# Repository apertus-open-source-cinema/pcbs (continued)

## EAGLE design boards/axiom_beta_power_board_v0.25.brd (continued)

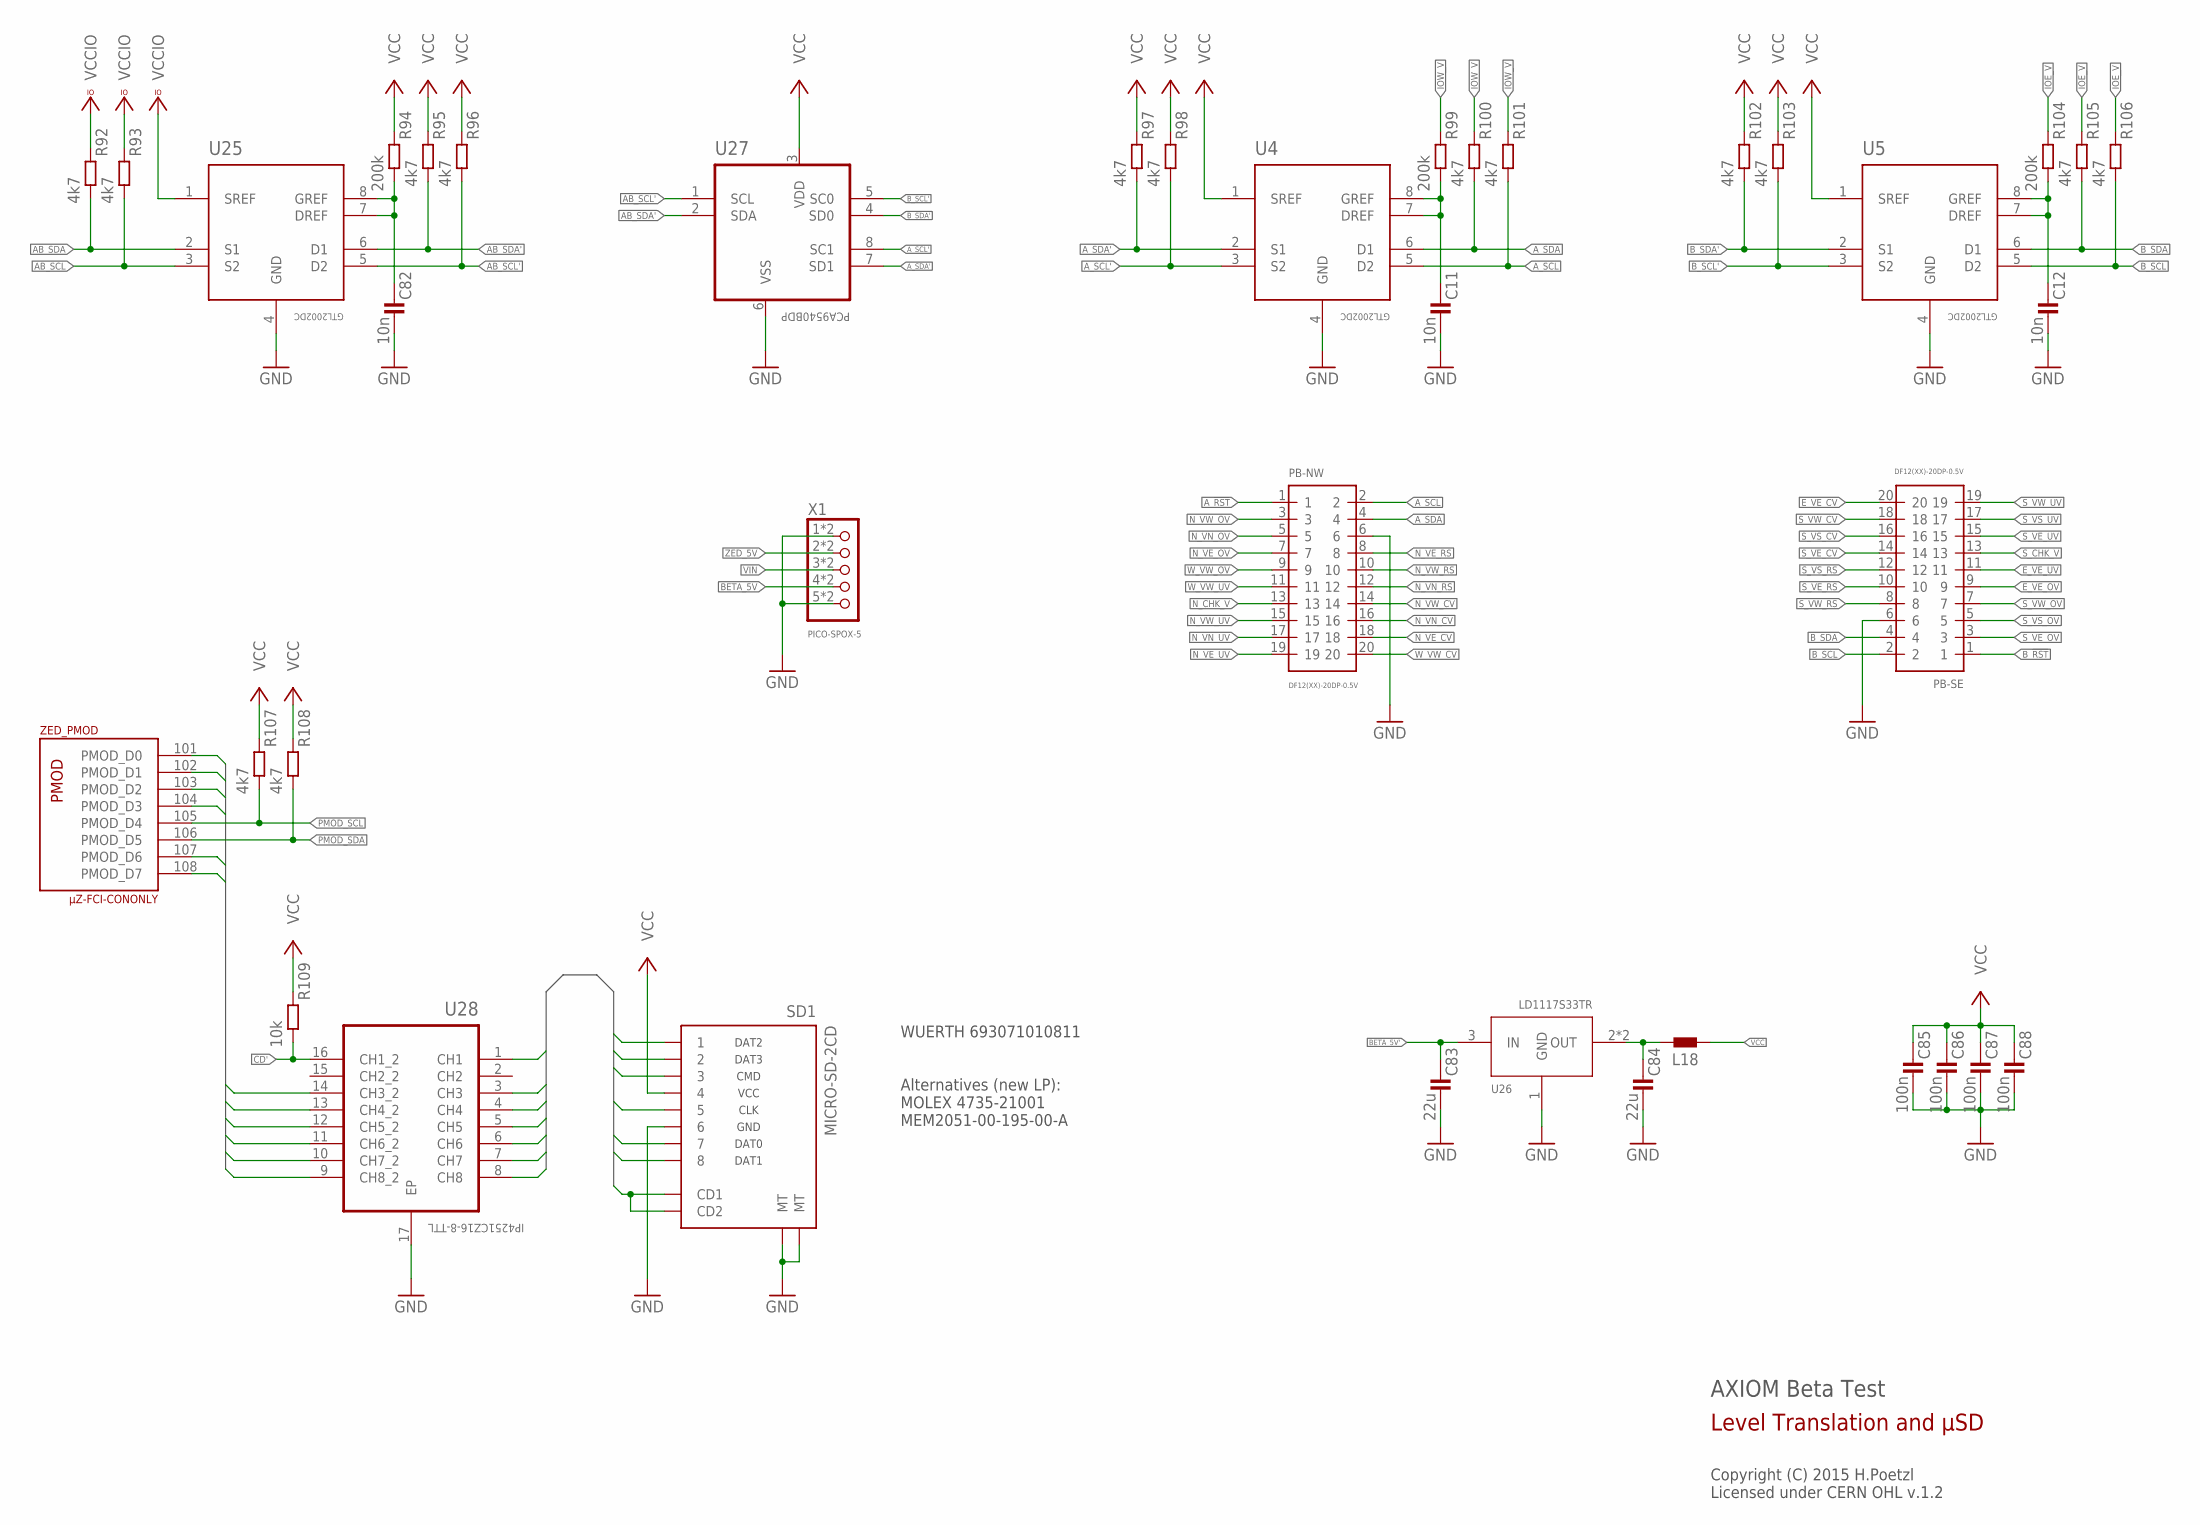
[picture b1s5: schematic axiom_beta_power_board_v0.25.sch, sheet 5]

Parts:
C11, C12, C82: 10n; 0402-B
C83, C84: 22u; 0805-B
C85, C86, C87, C88: 100n; 0402-B
L18: L0805-A; 0805-A
PB-NW: DF12(XX)-20DP-0.5V
PB-SE: DF12(XX)-20DP-0.5V
R92, R93, R95, R96, R97, R98, R100, R101, R102, R103, R105, R106, R107, R108: 4k7; 0402-B
R94, R99, R104: 200k; 0402-B
R109: 10k; 0402-B
SD1: MICRO-SD-2CD; TF-MICRO-SD_PP2
U4, U5, U25: GTL2002DC; VSSOP-8
U26: LD1117S33TR; SOT-223
U27: PCA9540BDP; SOP65P490X300-8N
U28: IP4251CZ16-8-TTL; SON40P135X330X55-17N
X1: PICO-SPOX-5
ZED: µZ-FCI-CONONLY; µZ-CONONLY

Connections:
AB_SCL: R93.2, U25.3 (S2); also elsewhere on the board
AB_SCL': R96.2, U25.5 (D2), U27.1 (SCL)
AB_SDA: R92.2, U25.2 (S1); also elsewhere on the board
AB_SDA': R95.2, U25.6 (D1), U27.2 (SDA)
A_!RST: PB-NW.1; also elsewhere on the board
A_SCL: PB-NW.2, R101.2, U4.5 (D2)
A_SCL': R98.2, U4.3 (S2), U27.8 (SC1)
A_SDA: PB-NW.4, R100.2, U4.6 (D1)
A_SDA': R97.2, U4.2 (S1), U27.7 (SD1)
BETA_5V: X1.4, X1.4A (4); also elsewhere on the board
BETA_5V': C83.1, U26.3 (IN); also elsewhere on the board
B_!RST: PB-SE.1; also elsewhere on the board
B_SCL: PB-SE.2, R106.2, U5.5 (D2)
B_SCL': R103.2, U5.3 (S2), U27.5 (SC0)
B_SDA: PB-SE.4, R105.2, U5.6 (D1)
B_SDA': R102.2, U5.2 (S1), U27.4 (SD0)
CD: SD1.CD1, SD1.CD2, U28.1 (CH1)
CD': R109.2, U28.16 (CH1_2); also elsewhere on the board
CLK: SD1.5, U28.6 (CH6)
CMD: SD1.3, U28.5 (CH5)
DAT0: SD1.7, U28.7 (CH7)
DAT1: SD1.8, U28.8 (CH8)
DAT2: SD1.1, U28.3 (CH3)
DAT3: SD1.2, U28.4 (CH4)
E_VE_CV: PB-SE.20
E_VE_OV: PB-SE.9
E_VE_UV: PB-SE.11
GND: C11.2, C12.2, C82.2, C83.2, C84.2, C85.2, C86.2, C87.2, C88.2, PB-NW.6, PB-SE.6, SD1.6, SD1.MT1 (MT), SD1.MT2 (MT), U4.4 (GND), U5.4 (GND), U25.4 (GND), U26.1 (GND), U27.6 (VSS), U28.17 (EP), X1.1, X1.1A (1), X1.5, X1.5A (5); also elsewhere on the board
IOE_V: R104.1, R105.1, R106.1; also elsewhere on the board
IOW_V: R99.1, R100.1, R101.1; also elsewhere on the board
unnamed: C11.1, R99.2, U4.7 (DREF), U4.8 (GREF)
unnamed: C12.1, R104.2, U5.7 (DREF), U5.8 (GREF)
unnamed: C82.1, R94.2, U25.7 (DREF), U25.8 (GREF)
N_CHK_V: PB-NW.13
N_VE_CV: PB-NW.18
N_VE_OV: PB-NW.7
N_VE_RS: PB-NW.8
N_VE_UV: PB-NW.19
N_VN_CV: PB-NW.16
N_VN_OV: PB-NW.5
N_VN_RS: PB-NW.12
N_VN_UV: PB-NW.17
N_VW_CV: PB-NW.14
N_VW_OV: PB-NW.3
N_VW_RS: PB-NW.10
N_VW_UV: PB-NW.15
PMOD_D0: U28.9 (CH8_2), ZED.101 (PMOD_D0)
PMOD_D1: U28.10 (CH7_2), ZED.102 (PMOD_D1)
PMOD_D2: U28.12 (CH5_2), ZED.103 (PMOD_D2)
PMOD_D3: U28.11 (CH6_2), ZED.104 (PMOD_D3)
PMOD_D6: U28.14 (CH3_2), ZED.107 (PMOD_D6)
PMOD_D7: U28.13 (CH4_2), ZED.108 (PMOD_D7)
PMOD_SCL: R107.2, ZED.105 (PMOD_D4); also elsewhere on the board
PMOD_SDA: R108.2, ZED.106 (PMOD_D5); also elsewhere on the board
REGOUT: C84.1, L18.1, U26.2 (OUT), U26.TER (OUT)
S_CHK_V: PB-SE.13
S_VE_CV: PB-SE.14
S_VE_OV: PB-SE.3
S_VE_RS: PB-SE.10
S_VE_UV: PB-SE.15
S_VS_CV: PB-SE.16
S_VS_OV: PB-SE.5
S_VS_RS: PB-SE.12
S_VS_UV: PB-SE.17
S_VW_CV: PB-SE.18
S_VW_OV: PB-SE.7
S_VW_RS: PB-SE.8
S_VW_UV: PB-SE.19
VCC: C85.1, C86.1, C87.1, C88.1, L18.2, R94.1, R95.1, R96.1, R97.1, R98.1, R102.1, R103.1, R107.1, R108.1, R109.1, SD1.4, U4.1 (SREF), U5.1 (SREF), U27.3 (VDD); also elsewhere on the board
VCCIO: R92.1, R93.1, U25.1 (SREF); also elsewhere on the board
VIN: X1.3, X1.3A (3)
W_VW_CV: PB-NW.20
W_VW_OV: PB-NW.9
W_VW_UV: PB-NW.11
ZED_5V: X1.2, X1.2A (2); also elsewhere on the board

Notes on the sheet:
AXIOM Beta Test
Copyright (C) 2015 H.Poetzl Licensed under CERN OHL v.1.2
Level Translation and µSD
WUERTH 693071010811 Alternatives (new LP): MOLEX 4735-21001 MEM2051-00-195-00-A

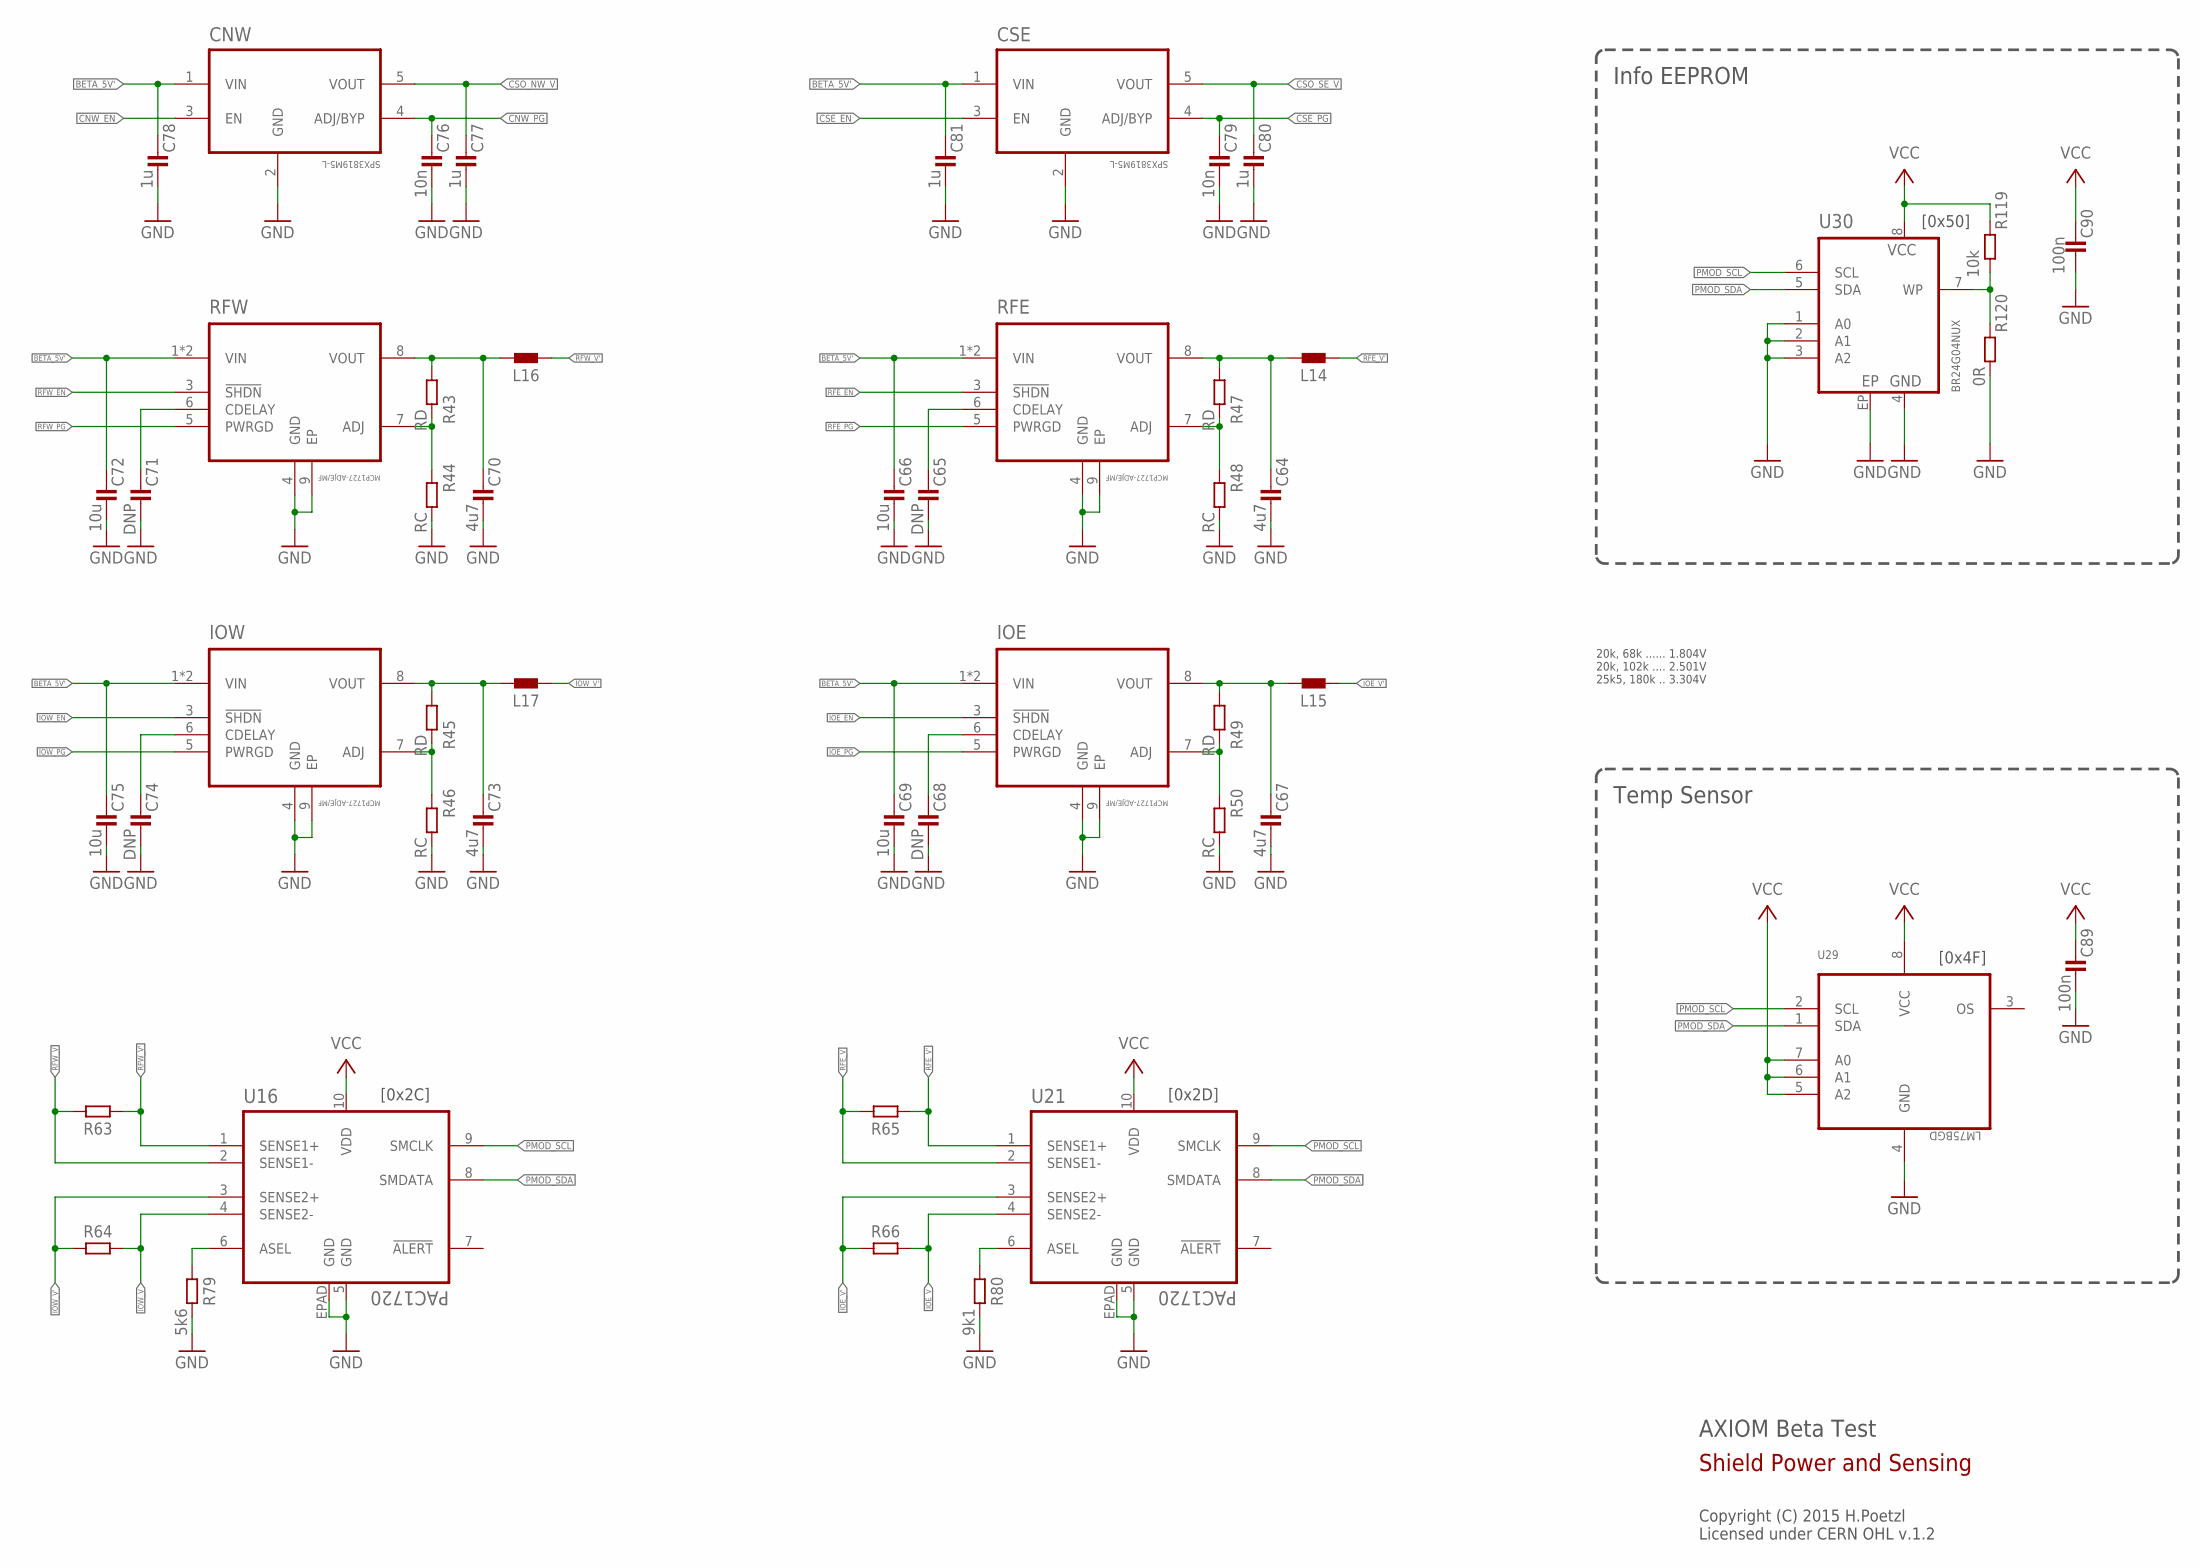
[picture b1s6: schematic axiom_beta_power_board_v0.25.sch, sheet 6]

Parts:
C64, C67, C70, C73: 4u7; 0603-B
C65, C68, C71, C74: DNP; 0402-B
C66, C69, C72, C75: 10u; 0603-B
C76, C79: 10n; 0402-B
C77, C78, C80, C81: 1u; 0402-B
C89, C90: 100n; 0402-B
CNW: SPX3819M5-L; SOT95P280X145-5N
CSE: SPX3819M5-L; SOT95P280X145-5N
IOE: MCP1727-ADJE/MF; DFN65P300X300X100-9N
IOW: MCP1727-ADJE/MF; DFN65P300X300X100-9N
L14, L15, L16, L17: L0805-B; 0805-B
R43, R45, R47, R49: RD; 0402-B
R44, R46, R48, R50: RC; 0402-B
R63, R64, R65, R66: R1206-B; 1206-B
R79: 5k6; 0402-B
R80: 9k1; 0402-B
R119: 10k; 0402-B
R120: 0R; 0402-B
RFE: MCP1727-ADJE/MF; DFN65P300X300X100-9N
RFW: MCP1727-ADJE/MF; DFN65P300X300X100-9N
U16, U21: PAC1720; DFN3X3_10LEAD
U29: LM75BGD; SOT996-2/3
U30: BR24G04NUX; DFN200X300X100-9N

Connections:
BETA_5V': C66.1, C69.1, C72.1, C75.1, C78.1, C81.1, CNW.1 (VIN), CSE.1 (VIN), IOE.1 (VIN), IOE.2 (VIN), IOW.1 (VIN), IOW.2 (VIN), RFE.1 (VIN), RFE.2 (VIN), RFW.1 (VIN), RFW.2 (VIN); also elsewhere on the board
CNW_EN: CNW.3 (EN); also elsewhere on the board
CNW_PG: C76.1, CNW.4 (ADJ/BYP); also elsewhere on the board
CSE_EN: CSE.3 (EN); also elsewhere on the board
CSE_PG: C79.1, CSE.4 (ADJ/BYP); also elsewhere on the board
CSO_NW_V: C77.1, CNW.5 (VOUT); also elsewhere on the board
CSO_SE_V: C80.1, CSE.5 (VOUT); also elsewhere on the board
GND: C64.2, C65.2, C66.2, C67.2, C68.2, C69.2, C70.2, C71.2, C72.2, C73.2, C74.2, C75.2, C76.2, C77.2, C78.2, C79.2, C80.2, C81.2, C89.2, C90.2, CNW.2 (GND), CSE.2 (GND), IOE.4 (GND), IOE.9 (EP), IOW.4 (GND), IOW.9 (EP), R44.2, R46.2, R48.2, R50.2, R79.2, R80.2, R120.2, RFE.4 (GND), RFE.9 (EP), RFW.4 (GND), RFW.9 (EP), U16.5 (GND), U16.EPAD (GND), U21.5 (GND), U21.EPAD (GND), U29.4 (GND), U30.1 (A0), U30.2 (A1), U30.3 (A2), U30.4 (GND), U30.EP; also elsewhere on the board
IOE_EN: IOE.3 (!SHDN); also elsewhere on the board
IOE_PG: IOE.5 (PWRGD); also elsewhere on the board
IOE_V: R66.2, U21.4 (SENSE2-); also elsewhere on the board
IOE_V': L15.2, R66.1, U21.3 (SENSE2+)
IOW_EN: IOW.3 (!SHDN); also elsewhere on the board
IOW_PG: IOW.5 (PWRGD); also elsewhere on the board
IOW_V: R64.2, U16.4 (SENSE2-); also elsewhere on the board
IOW_V': L17.2, R64.1, U16.3 (SENSE2+)
unnamed: R119.2, R120.1, U30.7 (WP)
unnamed: C64.1, L14.1, R47.1, RFE.8 (VOUT)
unnamed: R47.2, R48.1, RFE.7 (ADJ)
unnamed: C65.1, RFE.6 (CDELAY)
unnamed: C67.1, IOE.8 (VOUT), L15.1, R49.1
unnamed: IOE.7 (ADJ), R49.2, R50.1
unnamed: C68.1, IOE.6 (CDELAY)
unnamed: C70.1, L16.1, R43.1, RFW.8 (VOUT)
unnamed: R43.2, R44.1, RFW.7 (ADJ)
unnamed: C71.1, RFW.6 (CDELAY)
unnamed: C73.1, IOW.8 (VOUT), L17.1, R45.1
unnamed: IOW.7 (ADJ), R45.2, R46.1
unnamed: C74.1, IOW.6 (CDELAY)
unnamed: R79.1, U16.6 (ASEL)
unnamed: R80.1, U21.6 (ASEL)
PMOD_SCL: U16.9 (SMCLK), U21.9 (SMCLK), U29.2 (SCL), U30.6 (SCL); also elsewhere on the board
PMOD_SDA: U16.8 (SMDATA), U21.8 (SMDATA), U29.1 (SDA), U30.5 (SDA); also elsewhere on the board
RFE_EN: RFE.3 (!SHDN); also elsewhere on the board
RFE_PG: RFE.5 (PWRGD); also elsewhere on the board
RFE_V: R65.2, U21.2 (SENSE1-); also elsewhere on the board
RFE_V': L14.2, R65.1, U21.1 (SENSE1+)
RFW_EN: RFW.3 (!SHDN); also elsewhere on the board
RFW_PG: RFW.5 (PWRGD); also elsewhere on the board
RFW_V: R63.2, U16.2 (SENSE1-); also elsewhere on the board
RFW_V': L16.2, R63.1, U16.1 (SENSE1+)
VCC: C89.1, C90.1, R119.1, U16.10 (VDD), U21.10 (VDD), U29.5 (A2), U29.6 (A1), U29.7 (A0), U29.8 (VCC), U30.8 (VCC); also elsewhere on the board

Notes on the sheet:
AXIOM Beta Test
Copyright (C) 2015 H.Poetzl Licensed under CERN OHL v.1.2
Shield Power and Sensing
20k, 68k ...... 1.804V 20k, 102k .... 2.501V 25k5, 180k .. 3.304V
[0x2C]
[0x2D]
[0x4F]
Info EEPROM
[0x50]
Temp Sensor

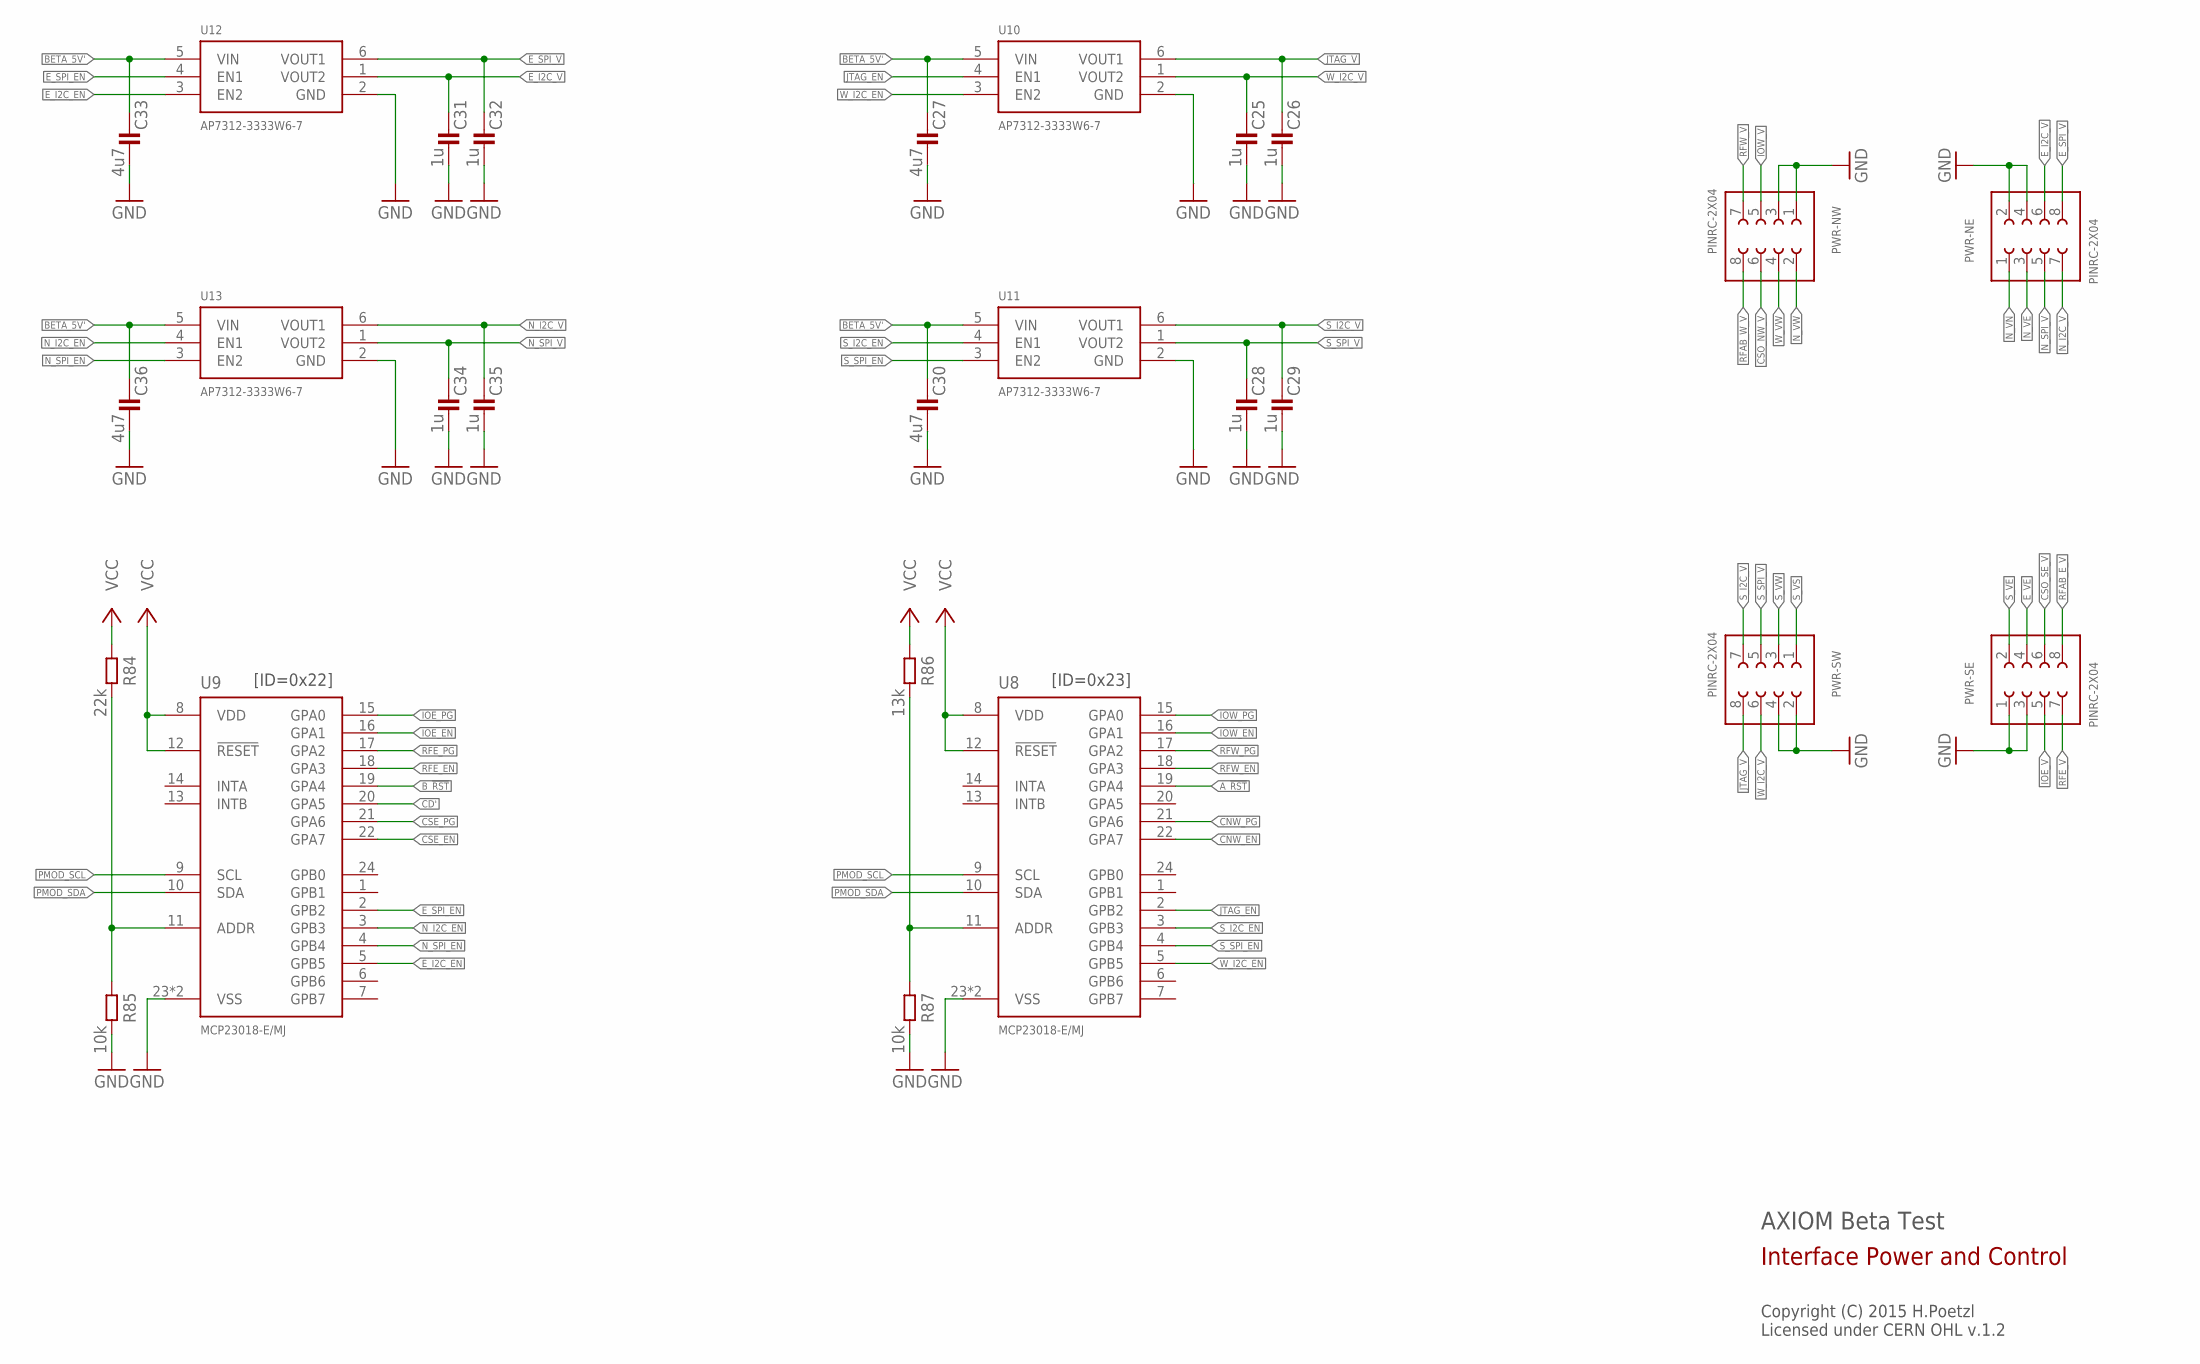
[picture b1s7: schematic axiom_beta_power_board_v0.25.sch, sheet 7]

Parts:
C25, C26, C28, C29, C31, C32, C34, C35: 1u; 0402-B
C27, C30, C33, C36: 4u7; 0603-B
PWR-NE: PINRC-2X04; R2X04
PWR-NW: PINRC-2X04; R2X04
PWR-SE: PINRC-2X04; R2X04
PWR-SW: PINRC-2X04; R2X04
R84: 22k; 0402-B
R85, R87: 10k; 0402-B
R86: 13k; 0402-B
U8, U9: MCP23018-E/MJ; QFN50P400X400X80-25N
U10, U11, U12, U13: AP7312-3333W6-7; SOT23-6

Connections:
A_!RST: U8.19 (GPA4); also elsewhere on the board
BETA_5V': C27.1, C30.1, C33.1, C36.1, U10.5 (VIN), U11.5 (VIN), U12.5 (VIN), U13.5 (VIN); also elsewhere on the board
B_!RST: U9.19 (GPA4); also elsewhere on the board
CD': U9.20 (GPA5); also elsewhere on the board
CNW_EN: U8.22 (GPA7); also elsewhere on the board
CNW_PG: U8.21 (GPA6); also elsewhere on the board
CSE_EN: U9.22 (GPA7); also elsewhere on the board
CSE_PG: U9.21 (GPA6); also elsewhere on the board
CSO_NW_V: PWR-NW.6; also elsewhere on the board
CSO_SE_V: PWR-SE.6; also elsewhere on the board
E_I2C_EN: U9.5 (GPB5), U12.3 (EN2)
E_I2C_V: C31.1, PWR-NE.6, U12.1 (VOUT2)
E_SPI_EN: U9.2 (GPB2), U12.4 (EN1)
E_SPI_V: C32.1, PWR-NE.8, U12.6 (VOUT1)
E_VE: PWR-SE.4; also elsewhere on the board
GND: C25.2, C26.2, C27.2, C28.2, C29.2, C30.2, C31.2, C32.2, C33.2, C34.2, C35.2, C36.2, PWR-NE.2, PWR-NE.4, PWR-NW.1, PWR-NW.3, PWR-SE.1, PWR-SE.3, PWR-SW.2, PWR-SW.4, R85.2, R87.2, U8.23 (VSS), U8.25 (VSS), U9.23 (VSS), U9.25 (VSS), U10.2 (GND), U11.2 (GND), U12.2 (GND), U13.2 (GND); also elsewhere on the board
IOE_EN: U9.16 (GPA1); also elsewhere on the board
IOE_PG: U9.15 (GPA0); also elsewhere on the board
IOE_V: PWR-SE.5; also elsewhere on the board
IOW_EN: U8.16 (GPA1); also elsewhere on the board
IOW_PG: U8.15 (GPA0); also elsewhere on the board
IOW_V: PWR-NW.5; also elsewhere on the board
JTAG_EN: U8.2 (GPB2), U10.4 (EN1)
JTAG_V: C26.1, PWR-SW.8, U10.6 (VOUT1)
unnamed: R84.2, R85.1, U9.11 (ADDR)
unnamed: R86.2, R87.1, U8.11 (ADDR)
N_I2C_EN: U9.3 (GPB3), U13.4 (EN1)
N_I2C_V: C35.1, PWR-NE.7, U13.6 (VOUT1)
N_SPI_EN: U9.4 (GPB4), U13.3 (EN2)
N_SPI_V: C34.1, PWR-NE.5, U13.1 (VOUT2)
N_VE: PWR-NE.3; also elsewhere on the board
N_VN: PWR-NE.1; also elsewhere on the board
N_VW: PWR-NW.2; also elsewhere on the board
PMOD_SCL: U8.9 (SCL), U9.9 (SCL); also elsewhere on the board
PMOD_SDA: U8.10 (SDA), U9.10 (SDA); also elsewhere on the board
RFAB_E_V: PWR-SE.8
RFAB_W_V: PWR-NW.8
RFE_EN: U9.18 (GPA3); also elsewhere on the board
RFE_PG: U9.17 (GPA2); also elsewhere on the board
RFE_V: PWR-SE.7; also elsewhere on the board
RFW_EN: U8.18 (GPA3); also elsewhere on the board
RFW_PG: U8.17 (GPA2); also elsewhere on the board
RFW_V: PWR-NW.7; also elsewhere on the board
S_I2C_EN: U8.3 (GPB3), U11.4 (EN1)
S_I2C_V: C29.1, PWR-SW.7, U11.6 (VOUT1)
S_SPI_EN: U8.4 (GPB4), U11.3 (EN2)
S_SPI_V: C28.1, PWR-SW.5, U11.1 (VOUT2)
S_VE: PWR-SE.2; also elsewhere on the board
S_VS: PWR-SW.1; also elsewhere on the board
S_VW: PWR-SW.3; also elsewhere on the board
VCC: R84.1, R86.1, U8.8 (VDD), U8.12 (!RESET), U9.8 (VDD), U9.12 (!RESET); also elsewhere on the board
W_I2C_EN: U8.5 (GPB5), U10.3 (EN2)
W_I2C_V: C25.1, PWR-SW.6, U10.1 (VOUT2)
W_VW: PWR-NW.4; also elsewhere on the board

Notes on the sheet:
AXIOM Beta Test
Copyright (C) 2015 H.Poetzl Licensed under CERN OHL v.1.2
Interface Power and Control
[ID=0x22]
[ID=0x23]

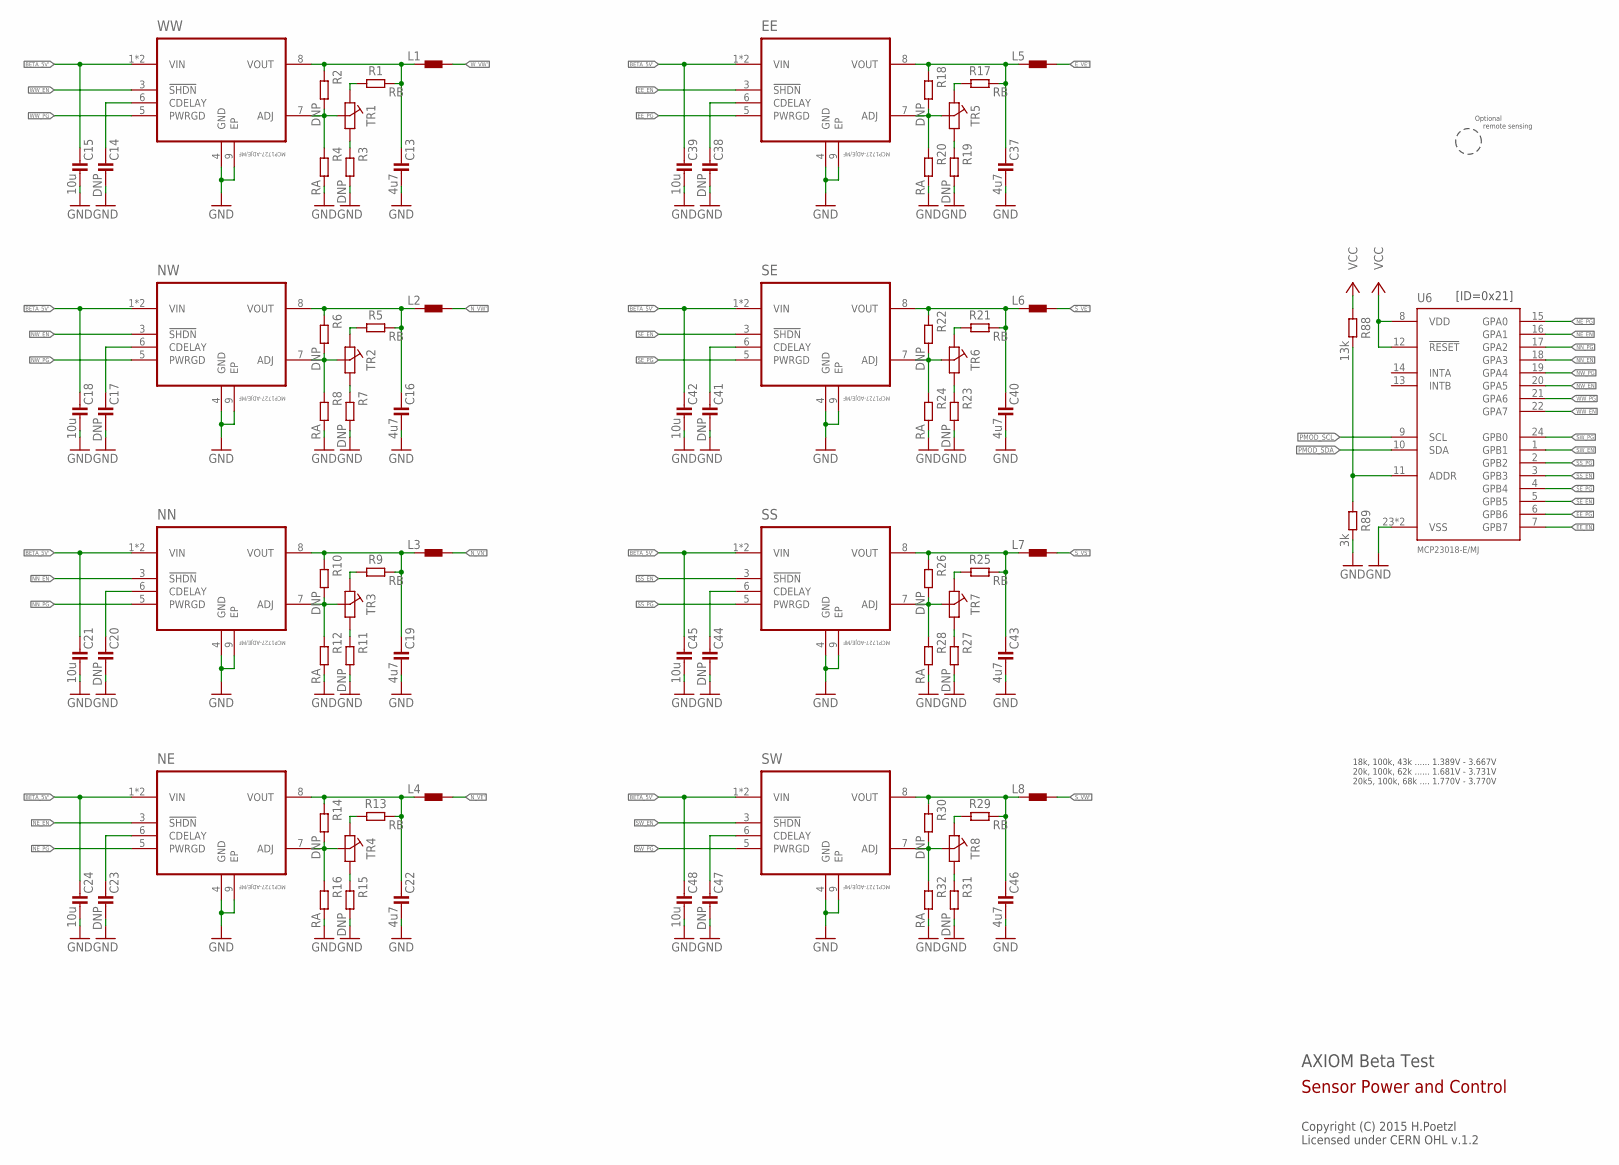
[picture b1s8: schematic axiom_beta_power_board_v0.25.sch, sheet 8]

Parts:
C13, C16, C19, C22, C37, C40, C43, C46: 4u7; 0603-B
C14, C17, C20, C23, C38, C41, C44, C47: DNP; 0402-B
C15, C18, C21, C24, C39, C42, C45, C48: 10u; 0603-B
EE: MCP1727-ADJE/MF; DFN65P300X300X100-9N
L1, L2, L3, L4, L5, L6, L7, L8: L0805-B; 0805-B
NE: MCP1727-ADJE/MF; DFN65P300X300X100-9N
NN: MCP1727-ADJE/MF; DFN65P300X300X100-9N
NW: MCP1727-ADJE/MF; DFN65P300X300X100-9N
R1, R5, R9, R13, R17, R21, R25, R29: RB; 0402-B
R2, R3, R6, R7, R10, R11, R14, R15, R18, R19, R22, R23, R26, R27, R30, R31: DNP; 0402-B
R4, R8, R12, R16, R20, R24, R28, R32: RA; 0402-B
R88: 13k; 0402-B
R89: 3k; 0402-B
SE: MCP1727-ADJE/MF; DFN65P300X300X100-9N
SS: MCP1727-ADJE/MF; DFN65P300X300X100-9N
SW: MCP1727-ADJE/MF; DFN65P300X300X100-9N
TR1, TR2, TR3, TR4, TR5, TR6, TR7, TR8: PVZ2A; TRIM-PVZ2A
U6: MCP23018-E/MJ; QFN50P400X400X80-25N
WW: MCP1727-ADJE/MF; DFN65P300X300X100-9N

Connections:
BETA_5V': C15.1, C18.1, C21.1, C24.1, C39.1, C42.1, C45.1, C48.1, EE.1 (VIN), EE.2 (VIN), NE.1 (VIN), NE.2 (VIN), NN.1 (VIN), NN.2 (VIN), NW.1 (VIN), NW.2 (VIN), SE.1 (VIN), SE.2 (VIN), SS.1 (VIN), SS.2 (VIN), SW.1 (VIN), SW.2 (VIN), WW.1 (VIN), WW.2 (VIN); also elsewhere on the board
EE_EN: EE.3 (!SHDN), U6.7 (GPB7)
EE_PG: EE.5 (PWRGD), U6.6 (GPB6)
E_VE': L5.2; also elsewhere on the board
GND: C13.2, C14.2, C15.2, C16.2, C17.2, C18.2, C19.2, C20.2, C21.2, C22.2, C23.2, C24.2, C37.2, C38.2, C39.2, C40.2, C41.2, C42.2, C43.2, C44.2, C45.2, C46.2, C47.2, C48.2, EE.4 (GND), EE.9 (EP), NE.4 (GND), NE.9 (EP), NN.4 (GND), NN.9 (EP), NW.4 (GND), NW.9 (EP), R3.2, R4.2, R7.2, R8.2, R11.2, R12.2, R15.2, R16.2, R19.2, R20.2, R23.2, R24.2, R27.2, R28.2, R31.2, R32.2, R89.2, SE.4 (GND), SE.9 (EP), SS.4 (GND), SS.9 (EP), SW.4 (GND), SW.9 (EP), U6.23 (VSS), U6.25 (VSS), WW.4 (GND), WW.9 (EP); also elsewhere on the board
unnamed: C13.1, L1.1, R1.2, R2.1, WW.8 (VOUT)
unnamed: R2.2, R4.1, TR1.2 (B), WW.7 (ADJ)
unnamed: R3.1, TR1.1 (A)
unnamed: C14.1, WW.6 (CDELAY)
unnamed: R1.1, TR1.3 (C)
unnamed: C16.1, L2.1, NW.8 (VOUT), R5.2, R6.1
unnamed: NW.7 (ADJ), R6.2, R8.1, TR2.2 (B)
unnamed: R7.1, TR2.1 (A)
unnamed: C17.1, NW.6 (CDELAY)
unnamed: C19.1, L3.1, NN.8 (VOUT), R9.2, R10.1
unnamed: NN.7 (ADJ), R10.2, R12.1, TR3.2 (B)
unnamed: R5.1, TR2.3 (C)
unnamed: C20.1, NN.6 (CDELAY)
unnamed: C22.1, L4.1, NE.8 (VOUT), R13.2, R14.1
unnamed: NE.7 (ADJ), R14.2, R16.1, TR4.2 (B)
unnamed: R11.1, TR3.1 (A)
unnamed: C23.1, NE.6 (CDELAY)
unnamed: C37.1, EE.8 (VOUT), L5.1, R17.2, R18.1
unnamed: EE.7 (ADJ), R18.2, R20.1, TR5.2 (B)
unnamed: R9.1, TR3.3 (C)
unnamed: C38.1, EE.6 (CDELAY)
unnamed: R15.1, TR4.1 (A)
unnamed: C40.1, L6.1, R21.2, R22.1, SE.8 (VOUT)
unnamed: R22.2, R24.1, SE.7 (ADJ), TR6.2 (B)
unnamed: R13.1, TR4.3 (C)
unnamed: C41.1, SE.6 (CDELAY)
unnamed: R19.1, TR5.1 (A)
unnamed: C43.1, L7.1, R25.2, R26.1, SS.8 (VOUT)
unnamed: R26.2, R28.1, SS.7 (ADJ), TR7.2 (B)
unnamed: R17.1, TR5.3 (C)
unnamed: C44.1, SS.6 (CDELAY)
unnamed: R23.1, TR6.1 (A)
unnamed: C46.1, L8.1, R29.2, R30.1, SW.8 (VOUT)
unnamed: R30.2, R32.1, SW.7 (ADJ), TR8.2 (B)
unnamed: R21.1, TR6.3 (C)
unnamed: C47.1, SW.6 (CDELAY)
unnamed: R27.1, TR7.1 (A)
unnamed: R25.1, TR7.3 (C)
unnamed: R31.1, TR8.1 (A)
unnamed: R29.1, TR8.3 (C)
unnamed: R88.2, R89.1, U6.11 (ADDR)
NE_EN: NE.3 (!SHDN), U6.16 (GPA1)
NE_PG: NE.5 (PWRGD), U6.15 (GPA0)
NN_EN: NN.3 (!SHDN), U6.18 (GPA3)
NN_PG: NN.5 (PWRGD), U6.17 (GPA2)
NW_EN: NW.3 (!SHDN), U6.20 (GPA5)
NW_PG: NW.5 (PWRGD), U6.19 (GPA4)
N_VE': L4.2; also elsewhere on the board
N_VN': L3.2; also elsewhere on the board
N_VW': L2.2; also elsewhere on the board
PMOD_SCL: U6.9 (SCL); also elsewhere on the board
PMOD_SDA: U6.10 (SDA); also elsewhere on the board
SE_EN: SE.3 (!SHDN), U6.5 (GPB5)
SE_PG: SE.5 (PWRGD), U6.4 (GPB4)
SS_EN: SS.3 (!SHDN), U6.3 (GPB3)
SS_PG: SS.5 (PWRGD), U6.2 (GPB2)
SW_EN: SW.3 (!SHDN), U6.1 (GPB1)
SW_PG: SW.5 (PWRGD), U6.24 (GPB0)
S_VE': L6.2; also elsewhere on the board
S_VS': L7.2; also elsewhere on the board
S_VW': L8.2; also elsewhere on the board
VCC: R88.1, U6.8 (VDD), U6.12 (!RESET); also elsewhere on the board
WW_EN: U6.22 (GPA7), WW.3 (!SHDN)
WW_PG: U6.21 (GPA6), WW.5 (PWRGD)
W_VW': L1.2; also elsewhere on the board

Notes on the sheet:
AXIOM Beta Test
Copyright (C) 2015 H.Poetzl Licensed under CERN OHL v.1.2
Sensor Power and Control
[ID=0x21]
18k, 100k, 43k ...... 1.389V - 3.667V 20k, 100k, 62k ...... 1.681V - 3.731V 20k5, 100k, 68k .... 1.770V - 3.770V
Optional remote sensing

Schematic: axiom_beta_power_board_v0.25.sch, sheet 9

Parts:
R51, R52, R53, R54, R55, R56, R57, R58, R59, R60, R61, R62: R1206-B; 1206-B
R73: 750R; 0402-B
R74: 1k27; 0402-B
R75: 430R; 0402-B
R76: 0R; 0402-B
R77: 100R; 0402-B
R78: 560R; 0402-B
U17, U18, U19, U20, U23, U24: PAC1720; DFN3X3_10LEAD

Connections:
E_VE: R57.2, U19.2 (SENSE1-); also elsewhere on the board
E_VE': R57.1, U19.1 (SENSE1+); also elsewhere on the board
GND: R73.2, R74.2, R75.2, R76.2, R77.2, R78.2, U17.5 (GND), U17.EPAD (GND), U18.5 (GND), U18.EPAD (GND), U19.5 (GND), U19.EPAD (GND), U20.5 (GND), U20.EPAD (GND), U23.5 (GND), U23.EPAD (GND), U24.5 (GND), U24.EPAD (GND); also elsewhere on the board
unnamed: R73.1, U18.6 (ASEL)
unnamed: R75.1, U24.6 (ASEL)
unnamed: R78.1, U23.6 (ASEL)
unnamed: R74.1, U20.6 (ASEL)
unnamed: R76.1, U19.6 (ASEL)
unnamed: R77.1, U17.6 (ASEL)
N_VE: R54.2, U20.4 (SENSE2-); also elsewhere on the board
N_VE': R54.1, U20.3 (SENSE2+); also elsewhere on the board
N_VN: R53.2, U20.2 (SENSE1-); also elsewhere on the board
N_VN': R53.1, U20.1 (SENSE1+); also elsewhere on the board
N_VW: R52.2, U18.4 (SENSE2-); also elsewhere on the board
N_VW': R52.1, U18.3 (SENSE2+); also elsewhere on the board
PCIE_VCCIO: R61.2, U23.2 (SENSE1-)
PMOD_SCL: U17.9 (SMCLK), U18.9 (SMCLK), U19.9 (SMCLK), U20.9 (SMCLK), U23.9 (SMCLK), U24.9 (SMCLK); also elsewhere on the board
PMOD_SDA: U17.8 (SMDATA), U18.8 (SMDATA), U19.8 (SMDATA), U20.8 (SMDATA), U23.8 (SMDATA), U24.8 (SMDATA); also elsewhere on the board
S_VE: R58.2, U19.4 (SENSE2-); also elsewhere on the board
S_VE': R58.1, U19.3 (SENSE2+); also elsewhere on the board
S_VS: R59.2, U17.2 (SENSE1-); also elsewhere on the board
S_VS': R59.1, U17.1 (SENSE1+); also elsewhere on the board
S_VW: R60.2, U17.4 (SENSE2-); also elsewhere on the board
S_VW': R60.1, U17.3 (SENSE2+); also elsewhere on the board
VCC: U17.10 (VDD), U18.10 (VDD), U19.10 (VDD), U20.10 (VDD), U23.10 (VDD), U24.10 (VDD); also elsewhere on the board
VCCIO: R55.1, R56.1, R61.1, R62.1, U23.1 (SENSE1+), U23.3 (SENSE2+), U24.1 (SENSE1+), U24.3 (SENSE2+); also elsewhere on the board
VCCO_13: R56.2, U24.4 (SENSE2-); also elsewhere on the board
VCCO_34: R62.2, U23.4 (SENSE2-); also elsewhere on the board
VCCO_35: R55.2, U24.2 (SENSE1-); also elsewhere on the board
W_VW: R51.2, U18.2 (SENSE1-); also elsewhere on the board
W_VW': R51.1, U18.1 (SENSE1+); also elsewhere on the board

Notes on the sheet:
AXIOM Beta Test
Copyright (C) 2015 H.Poetzl Licensed under CERN OHL v.1.2
Sensor Power Sensing
[0x48]
[0x49]
[0x4B]
[0x4D]
[0x4A]
[0x4C]
